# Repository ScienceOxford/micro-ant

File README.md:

# micro-ant

### Click here to find all the information: <a href="https://scienceoxford.github.io/micro-ant" target="_blank">micro-ant</a>

Work in progress!

*Developed by [ScienceOxford](https://scienceoxford.com) for educational purposes. Please give credit where applicable.
<br>We love seeing what you've created, so tag us when you share! [@ScienceOxford](https://twitter.com/scienceoxford)*

<br />This work is licensed under a <a rel="license" href="http://creativecommons.org/licenses/by-sa/4.0/">Creative Commons Attribution-ShareAlike 4.0 International License</a>.

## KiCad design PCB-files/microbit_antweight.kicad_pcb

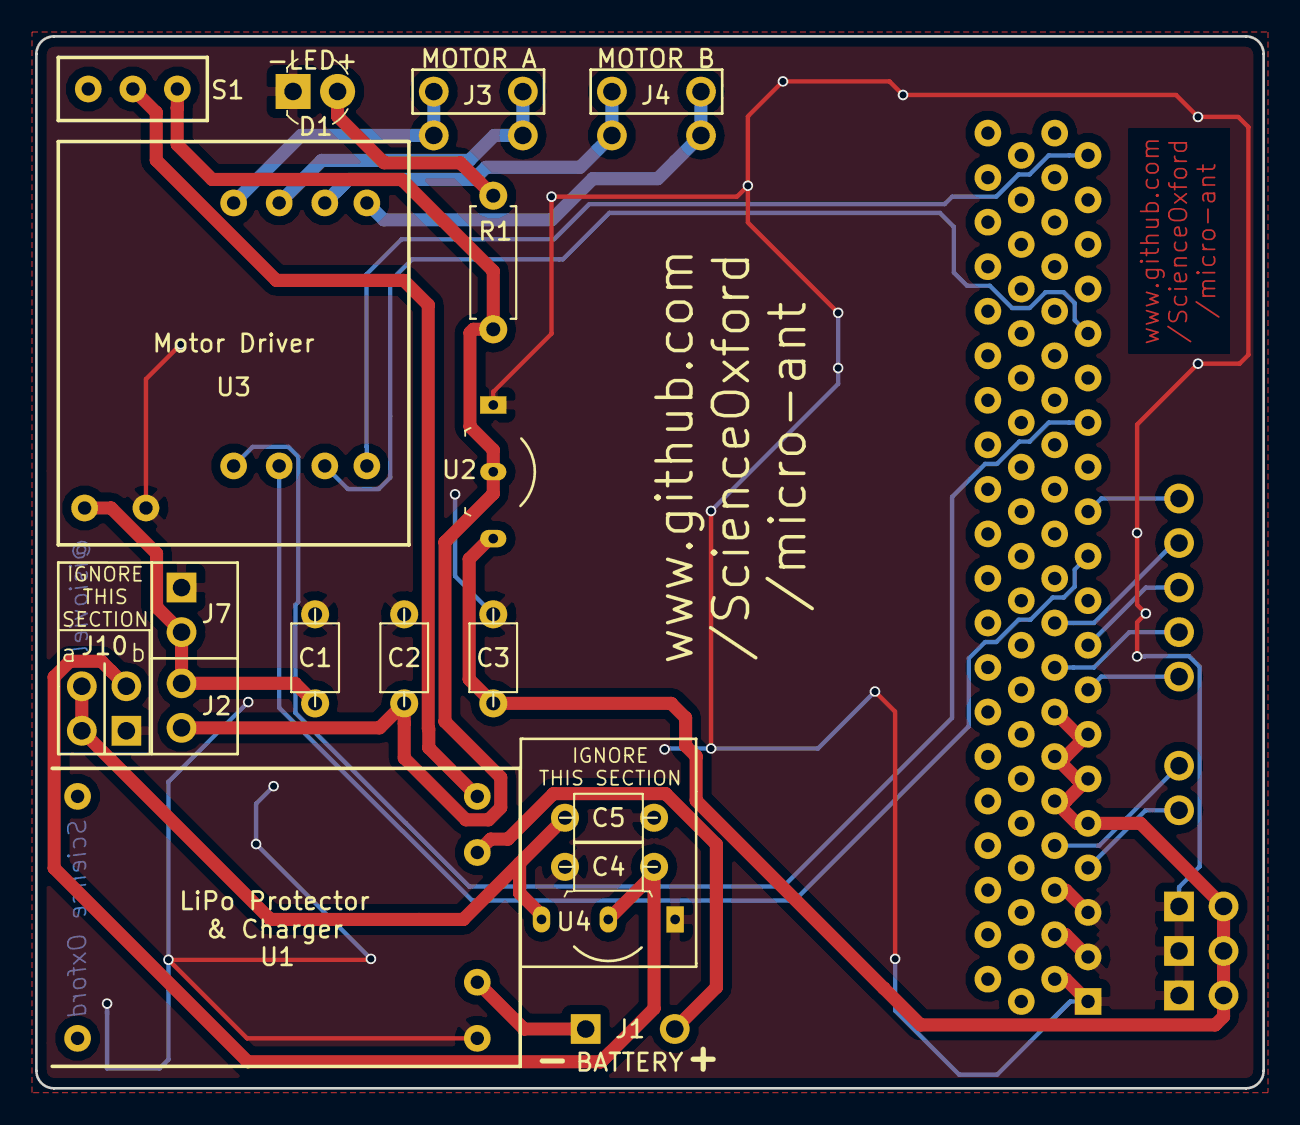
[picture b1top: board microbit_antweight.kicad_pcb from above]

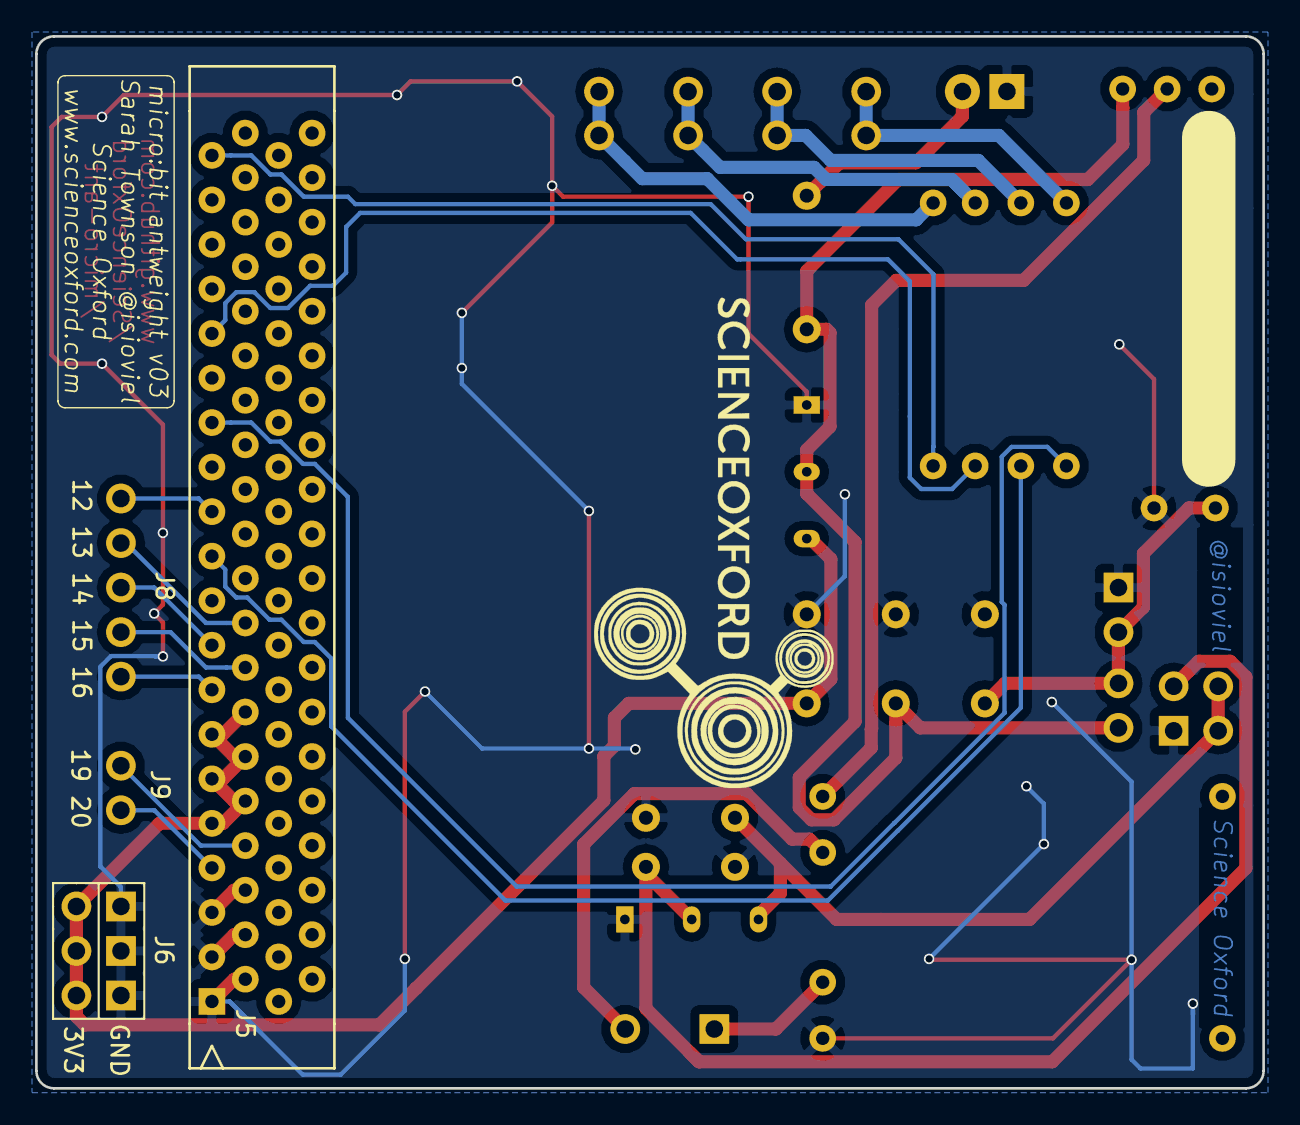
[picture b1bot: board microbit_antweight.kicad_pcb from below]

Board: 2 copper layers, 70.0 x 60.0 mm, 22 parts (4 on the bottom side), 25 nets.

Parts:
C1, C2, C3, C4, C5: 1uF; C_Axial_L3.8mm_D2.6mm_P5.0mm_Horizontal
D1: LED; LED_3mm_Radial
J1: Conn_BAT; Pin_Header_Straight_1x02_Pitch_large_battery
J2: Conn_MOT_INT; Pin_Header_Straight_1x02_Pitch2.54mm
J3: Conn_MOT_B; Pin_Header_Straight_1x02_Pitch_large_doubled
J4: Conn_MOT_A; Pin_Header_Straight_1x02_Pitch_large_doubled
J5: microbit_edge_connector
J6: Conn_POW; Pin_Header_Straight_2x03_Pitch2.54mm
J7: Conn_MOT_EXT; Pin_Header_Straight_1x02_Pitch2.54mm_battery
J8: Conn_PINS; Pin_Header_Straight_1x05_Pitch2.54mm
J9: Conn_SER; Pin_Header_Straight_1x02_Pitch2.54mm
J10: Conn_REG; Pin_Header_Straight_2x02_Pitch2.54mm
R1: 100; R_Axial_DIN0207_L6.3mm_D2.5mm_P7.62mm_Horizontal
S1: switch; slide_switch
U1: LipoCharger
U2: MCP1700-3302E_TO92; TO-92-3
U3: MotorDriver
U4: MCP1702-5002E_TO92; TO-92-3

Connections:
5V: C5.1, J10.1, J10.3, U4.3
GND: C1.1, C2.1, C3.1, C4.1, C5.2, D1.1, J5.1, J5.3, J5.5, J5.7, J5.9, J5.11, J6.2, J6.4, J6.6, J7.2, J10.4, U1.3, U2.1, U3.2, U4.1
MB0: J5.77, U3.6
MB1: J5.61, U3.5
MB2: J5.41, U3.4
MB8: J5.53, U3.3
unnamed: C1.2, J2.2, J7.1, U3.1
unnamed: C2.2, J2.1, R1.2, S1.1, U2.2
unnamed: C4.2, J10.2, U4.2
unnamed: D1.2, R1.1
unnamed: J1.1, U1.5
unnamed: J1.2, U1.4
unnamed: J3.1, U3.10
unnamed: J3.2, U3.9
unnamed: J4.1, U3.8
unnamed: J4.2, U3.7
unnamed: S1.2, U1.6
P3V3: C3.2, J5.17, J5.19, J5.21, J5.23, J5.25, J5.27, J6.1, J6.3, J6.5, U2.3
P12: J5.45, J8.1
P13: J5.35, J8.2
P14: J5.33, J8.3
P15: J5.31, J8.4
P16: J5.29, J8.5
P_19: J5.15, J9.1
P_20: J5.13, J9.2

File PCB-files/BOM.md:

# Bill of Materials

| Designator         | Package                                          | Quant | Designation        | Example Supplier                                                            |
| ------------------ | ------------------------------------------------ | ----- | ------------------ | --------------------------------------------------------------------------- |
| C1, C2, C3, C4, C5 | C_Axial_L3.8mm_D2.6mm_P5.0mm_Horizontal          | 3     | 1uF                | <https://www.aliexpress.com/item/32848919879.html> |
| D1                 | LED_3mm_Radial                                   | 1     |                    |  |
| J1                 | XH plug connector                                | 1     |                    | <https://www.aliexpress.com/item/32761581540.html> |
| J1                 | 3.7V 1S LiPo Battery (XH plug)                   | 1     |                    | <https://www.aliexpress.com/item/32846780139.html> |
| J2, U1, U3         | Pin Header (Male) Straight Pitch 2.54mm          | 18    |                    |  |
| J2                 | Pin header jumper connector 2.54mm pitch         | 1     |                    | <https://www.aliexpress.com/item/32827199777.html> |
| J3, J4             | Flexible wire ~24AWG                             |       |                    |  |
| J3, J4             | N20 motor 3V ~300RPM                             | 2     |                    | <https://www.aliexpress.com/item/32913728217.html> |
| J5                 | microbit_edge_connector (Kitronik)               | 1     |                    | <https://www.kitronik.co.uk/4148-edge-connector-header-for-bb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 |
| J5                 | Thick tape to raise the edge connector ~2mm      |       |                    |  |
| R1                 | R_Axial_DIN0207_L6.3mm_D2.5mm_P7.62mm_Horizontal | 1     | 100                |  |
| S1                 | slide_switch                                     | 1     |                    | <https://www.amazon.co.uk/gp/product/B06XK9V582> |
| U1                 | LipoCharger                                      | 1     |                    | <https://www.aliexpress.com/item/32761199508.html> |
| U2                 | TO-92-3                                          | 1     | MCP1700-3302E_TO92 | <https://www.aliexpress.com/item/32952835501.html> |
| U3                 | MotorDriver                                      | 1     |                    | <https://www.aliexpress.com/item/32646270295.html> |
| U4                 | TO-92-3                                          | 1     | MCP1702-5002E_TO92 | <https://www.aliexpress.com/item/32849044125.html> |
|                    | BBC micro:bit                                    | 1     |                    | <https://www.kitronik.co.uk/5615-bbc-microbit-starter-kit.html> |
| C4, C5             | C_Axial_L3.8mm_D2.6mm_P5.0mm_Horizontal          | 1     | 1uF                | OPTIONAL |
| J3, J4             | C_Axial_L3.8mm_D2.6mm_P5.0mm_Horizontal          | 1     | 0.1uF              | OPTIONAL |
| J6, J8, J9, J10a   | Pin Header (Male) Straight Pitch 2.54mm          | 15    |                    | OPTIONAL |
| J7, J10b           | external battery and appropriate connector cable | 1     |                    | OPTIONAL |
| U1, U3             | Pin Header (Female) Straight Pitch 2.54mm        | 16    |                    | OPTIONAL |

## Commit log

2019-09-10 Rename step5.py to step4.py
2019-09-10 Rename step6.py to step5.py
2019-09-24 Set theme jekyll-theme-slate
2019-10-01 adding speaker instructions
2019-10-01 added pin soldering instructions
2019-10-02 add some soldering images
2019-10-15 final pins images
2019-10-16 adding files for ccc
2019-10-18 extensions
2019-10-18 minor edits
2019-10-18 TEMP EDITS
    revert after Creative Computing Club, before Robocamp follow-up
2019-10-21 Update robot_starter.py
    add sleep
2019-10-21 revert edit
    back to links for Robocamp
2019-10-22 robocamp-followup
    add servo & bumper instructions
2019-10-24 instructions for body design
2019-11-12 makecode
    Added working robot & controller code for MakeCode
2019-11-12 v3 pcb files
    Added schematic + board files, custom libraries & bill of materials
2019-11-12 Update body.html
    editing to make it less workshop specific
2019-11-15 increase font size
2020-09-03 Create LICENSE
2020-10-21 docs: add video
2022-07-08 Update joystick_working+buttons.py
    update button range
2022-07-08 Update joystick_working.py
    update button range
2022-07-08 Update joystick_buttons.py
    update button range
2022-07-08 Update joystick_left_right.py
    update button range
2022-07-08 Update joystick_setup.py
    update button range

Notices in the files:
PCB-files/microbit_antweight.kicad_pcb:
License: CC BY-SA 4.0
